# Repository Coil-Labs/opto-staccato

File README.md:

# opto-staccato

## Introduction
This is a pair of circuit boards (PCBs), known as the Opto-Staccato Controller and Receiver, which are a mains frequency synchronized interrupter for Tesla coils, primarily vacuum tube Tesla coils (VTTCs).

This circuit is based on the original Staccato Controller, created by Steve Ward https://www.stevehv.4hv.org/staccato.htm

This circuit is featured on the Coil Labs YouTube channel and is used to interrupt a large VTTC (https://youtu.be/IDOrxT_r8TY). This project was sponsored in part by PCBgogo (https://www.pcbgogo.com/), who provided the PCBs for this video.

The KiCad source files for both boards are available in this repository and the gerber files for both boards are available as .zip files in the Releases.

## Description

The Controller PCB detects the mains frequency zero crossing and then sends a pulse to the Receiver (with a controllable delay based on potentiometer RV1), signaling when to let the Tesla coil primary circuit to begin conducting. This signal is sent over a fiber optic link to protect the user from coming into contact with high voltage and enabling them to maintain a safe distance from the Tesla coil. The other controllable parameter (set by potentiometer RV2) of the Controller is the interrupter hold-off time, which enables the Tesla coil to be driven at integer factors of the mains frequency (e.g., 60 Hz, 30 Hz, 15 Hz, etc. in North America).

## Safety
WARNING! High voltage electricity and Tesla coils are dangerous and should not be handled or operated by anyone other than trained experts! 

## Usage
Jumpers J5 and J6 on the Controller and J7 and J8 on the Receiver enable using the PCBs in either 120V or 240V mains regions. Place two jumpers across pins 1 and 2 of both jumpers for 120V use or a single jumper across pin 2 of the two jumpers for 240V use, as indicated on the silk screen.

On the Controller, switch SW1 is the "phase-select" choosing to trigger the circuit on either the rising or falling mains zero crossing. Switch Sw2 is the "output-enable" switch, allowing the user to control when the Tesla coil interrupter is "turned on". Switch Sw3 selects the source of the signal being sent out via the fiber optic link; either the Staccato signal, "always on" for continuous wave operation, or an optional external 0-12V digital signal that can be provided via screw terminal J2.

The SCR or TRIAC used for Staccato operation is not included on the Receiver PCB as the choice of this component is specific to each Tesla coil. A screw terminal block J4 is provided to connect to the gate and cathode terminals for triggering. The selection of resistor R22 may need to be changed, depending on the gate voltage and current requirements of the SCR/TRIAC being used.

The fiber optic transmitter and receiver use standard 1000um core, 2.2mm jacket plastic fiber cable. The fuses are 500mA, 250V, fast blow, glass cartridge, 5mm x 20mm.

## License
These design files are published under the CERN Open Hardware License Version 2 - Weakly Reciprocal variant (CERN-OHL-W). Read more here (https://cern.ch/cern-ohl).

This is a copyleft, share-alike, open-source license. This means that you are free to redistribute, modify, or make derivatives these designs, and even commercialize them. But you MUST keep the redistributed, modified, or derivative designs open-source and under this or a compatible license. You CANNOT make modified or derivative designs proprietary; they MUST be kept open-source. This is different than a "permissive" open-source license, where you can make modifications or derivatives proprietary and then commercialize and profit off of your proprietary modification. You are absolutely free to commercialize and profit from modifications of this design, however, it must remain open-source and accessible to the public. Copyleft, share-alike is a philosophy. Scientific and engineering knowledge should not be kept as trade secrets and locked down under patents, owned by the wealthy, to only benefit the wealthy. Knowledge should be freely shared, always. Publishing scientific and engineering works under copyleft, share-alike licenses helps to create a more fair and democratic future where the hoarding of trade secrets is not a way to gain a competitive advantage. Please consider publishing your own works under such a license.

## Controller Schematic

## Receiver Schematic

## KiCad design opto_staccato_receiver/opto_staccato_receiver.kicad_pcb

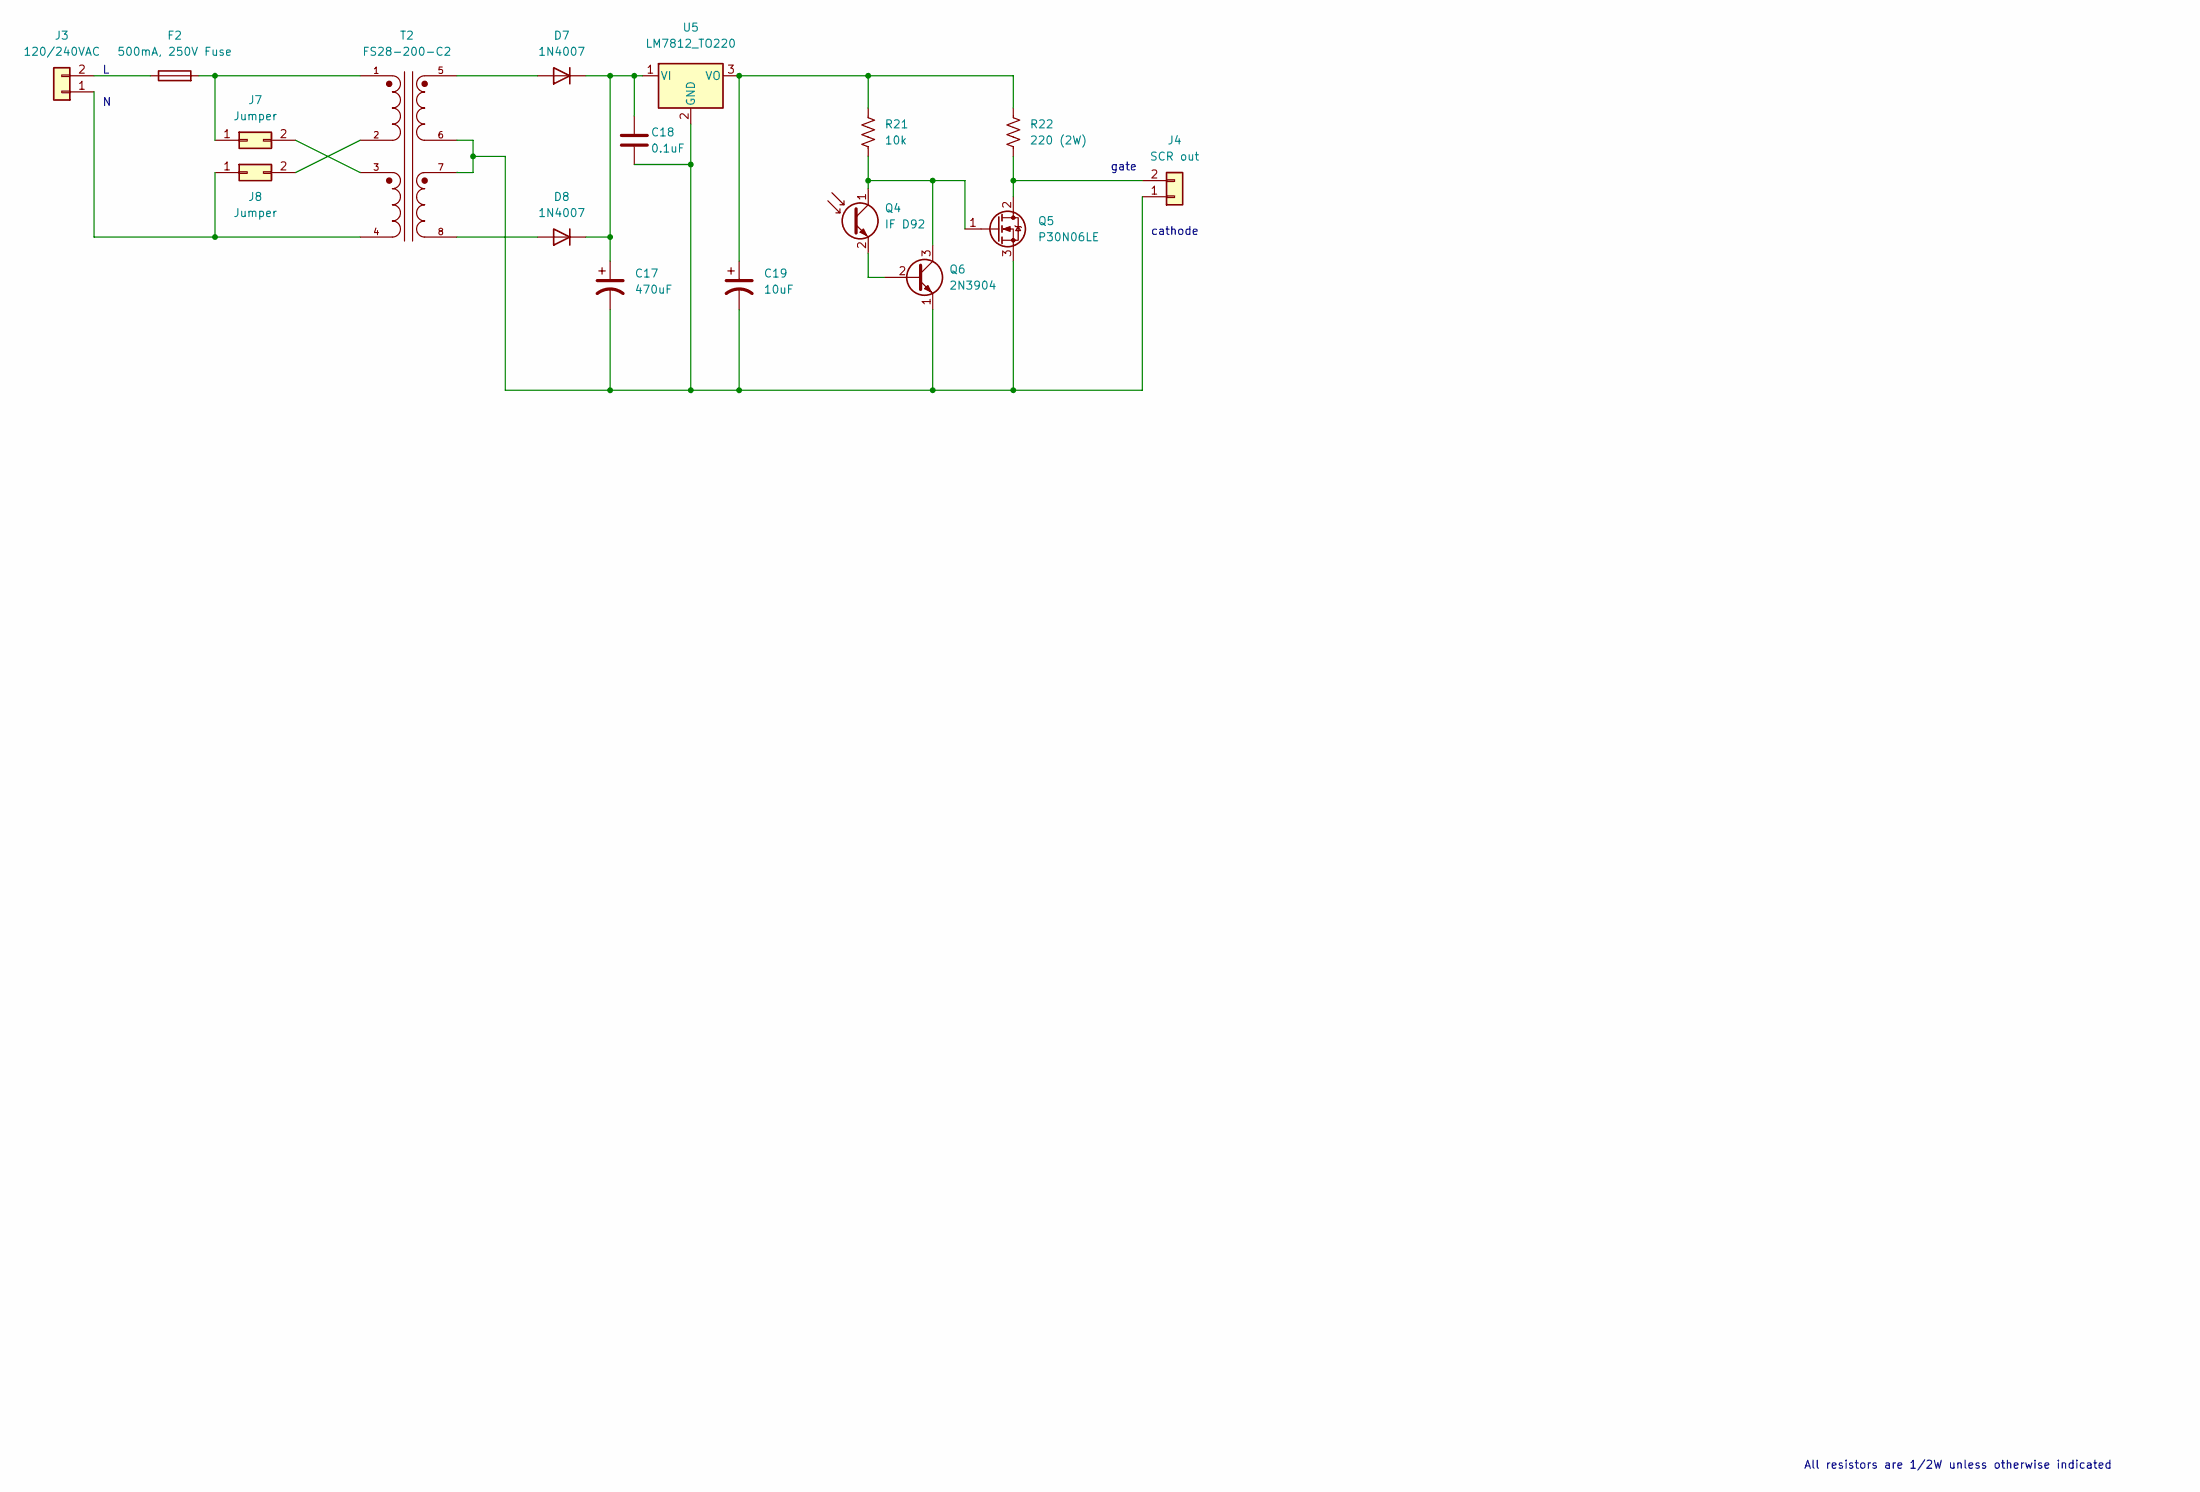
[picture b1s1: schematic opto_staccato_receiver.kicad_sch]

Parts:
C17: 470uF; CP_Radial_D10.0mm_P5.00mm
C18: 0.1uF; C_Disc_D4.7mm_W2.5mm_P5.00mm
C19: 10uF; CP_Radial_D5.0mm_P2.00mm
D7, D8: 1N4007; D_DO-41_SOD81_P10.16mm_Horizontal
F2: 500mA, 250V Fuse; 0PTF0078P
J3: 120/240VAC; SolderWire-1sqmm_1x02_P5.4mm_D1.4mm_OD2.7mm
J4: SCR out; CUI_TB007-508-02GR
J7, J8: Jumper; PinHeader_2x01_P2.54mm_Vertical
Q4: IF D92; IF-E91A
Q5: P30N06LE; TO-220-3_Vertical
Q6: 2N3904; TO-92_Inline
R21: 10k; R_Axial_DIN0309_L9.0mm_D3.2mm_P12.70mm_Horizontal
R22: 220 (2W); R_Axial_DIN0516_L15.5mm_D5.0mm_P20.32mm_Horizontal
T2: FS28-200-C2; TRANSFORMER_FS28-200-C2
U5: LM7812_TO220; TO-220-3_Vertical

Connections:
unnamed: C17.1, C18.1, D7.1 (K), D8.1 (K), U5.1 (VI)
unnamed: C17.2, C18.2, C19.2, J4.1, Q5.3 (S), Q6.1 (E), T2.6, T2.7, U5.2 (GND)
unnamed: C19.1, R21.1, R22.1, U5.3 (VO)
unnamed: D7.2 (A), T2.5
unnamed: D8.2 (A), T2.8
unnamed: F2.1, J3.2
unnamed: F2.2, J7.1, T2.1
unnamed: J3.1, J8.1, T2.4
unnamed: J4.2, Q5.2 (D), R22.2
unnamed: J7.2, T2.3
unnamed: J8.2, T2.2
unnamed: Q4.1 (C), Q5.1 (G), Q6.3 (C), R21.2
unnamed: Q4.2 (E), Q6.2 (B)

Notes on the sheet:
gate
cathode
All resistors are 1/2W unless otherwise indicated

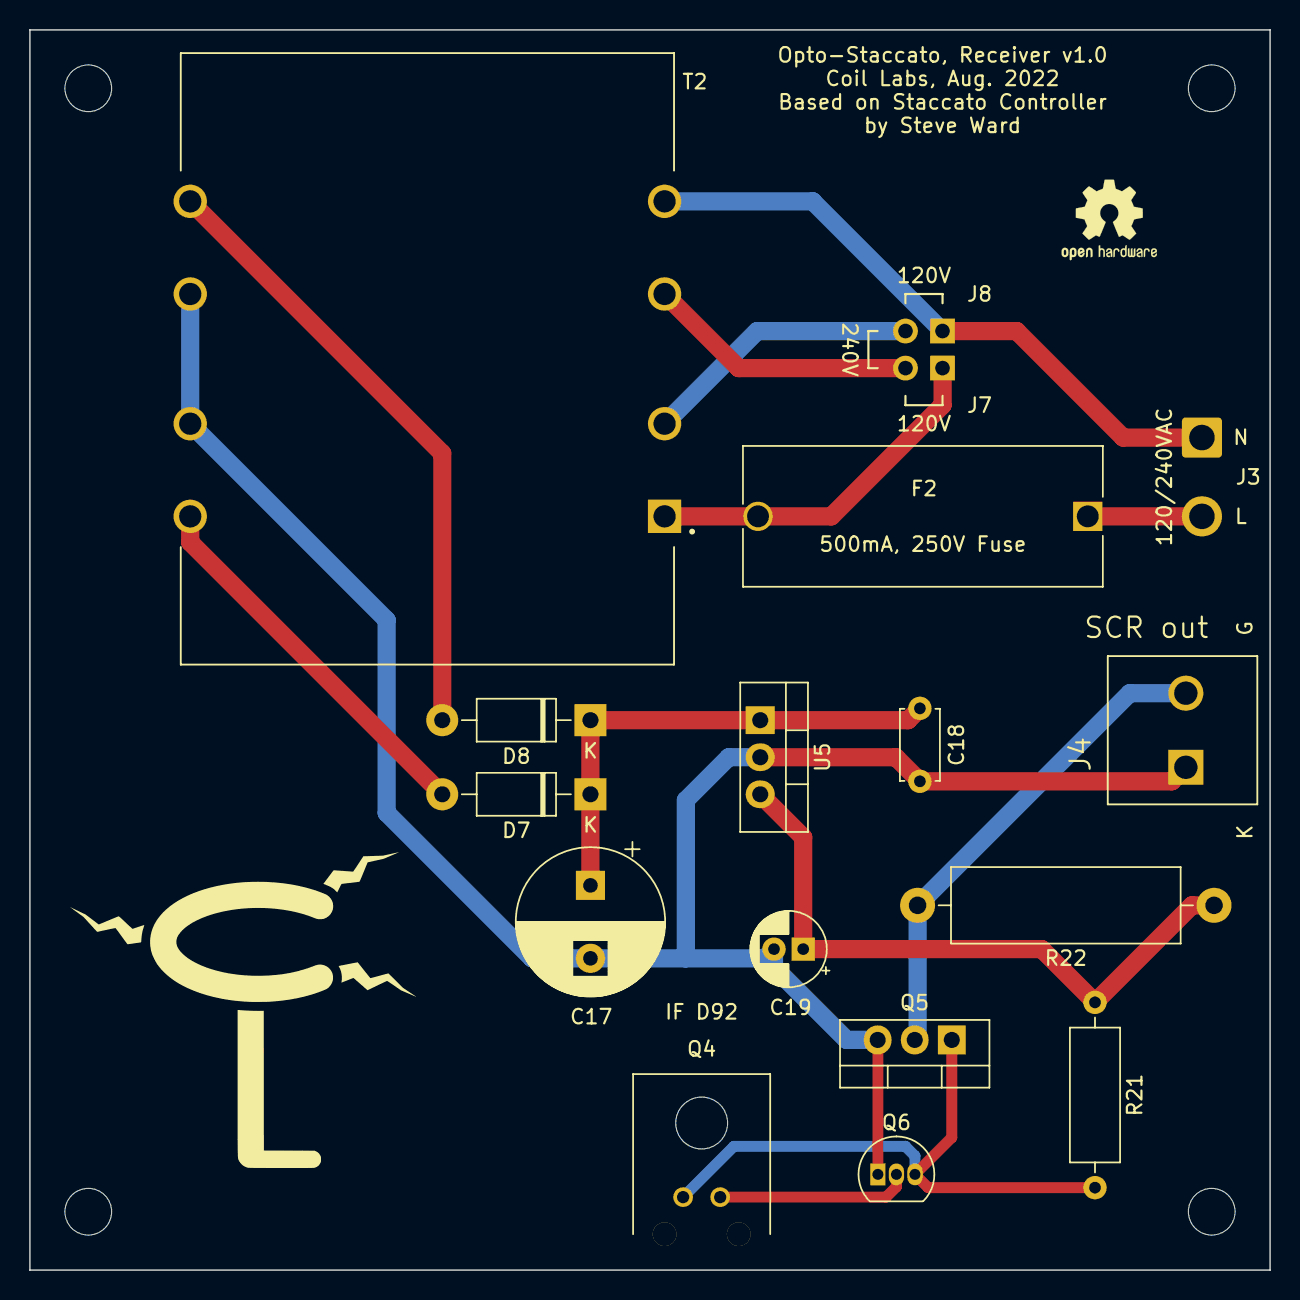
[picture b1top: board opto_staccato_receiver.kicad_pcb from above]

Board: 2 copper layers, 85.0 x 85.0 mm, 17 parts (0 on the bottom side), 13 nets.

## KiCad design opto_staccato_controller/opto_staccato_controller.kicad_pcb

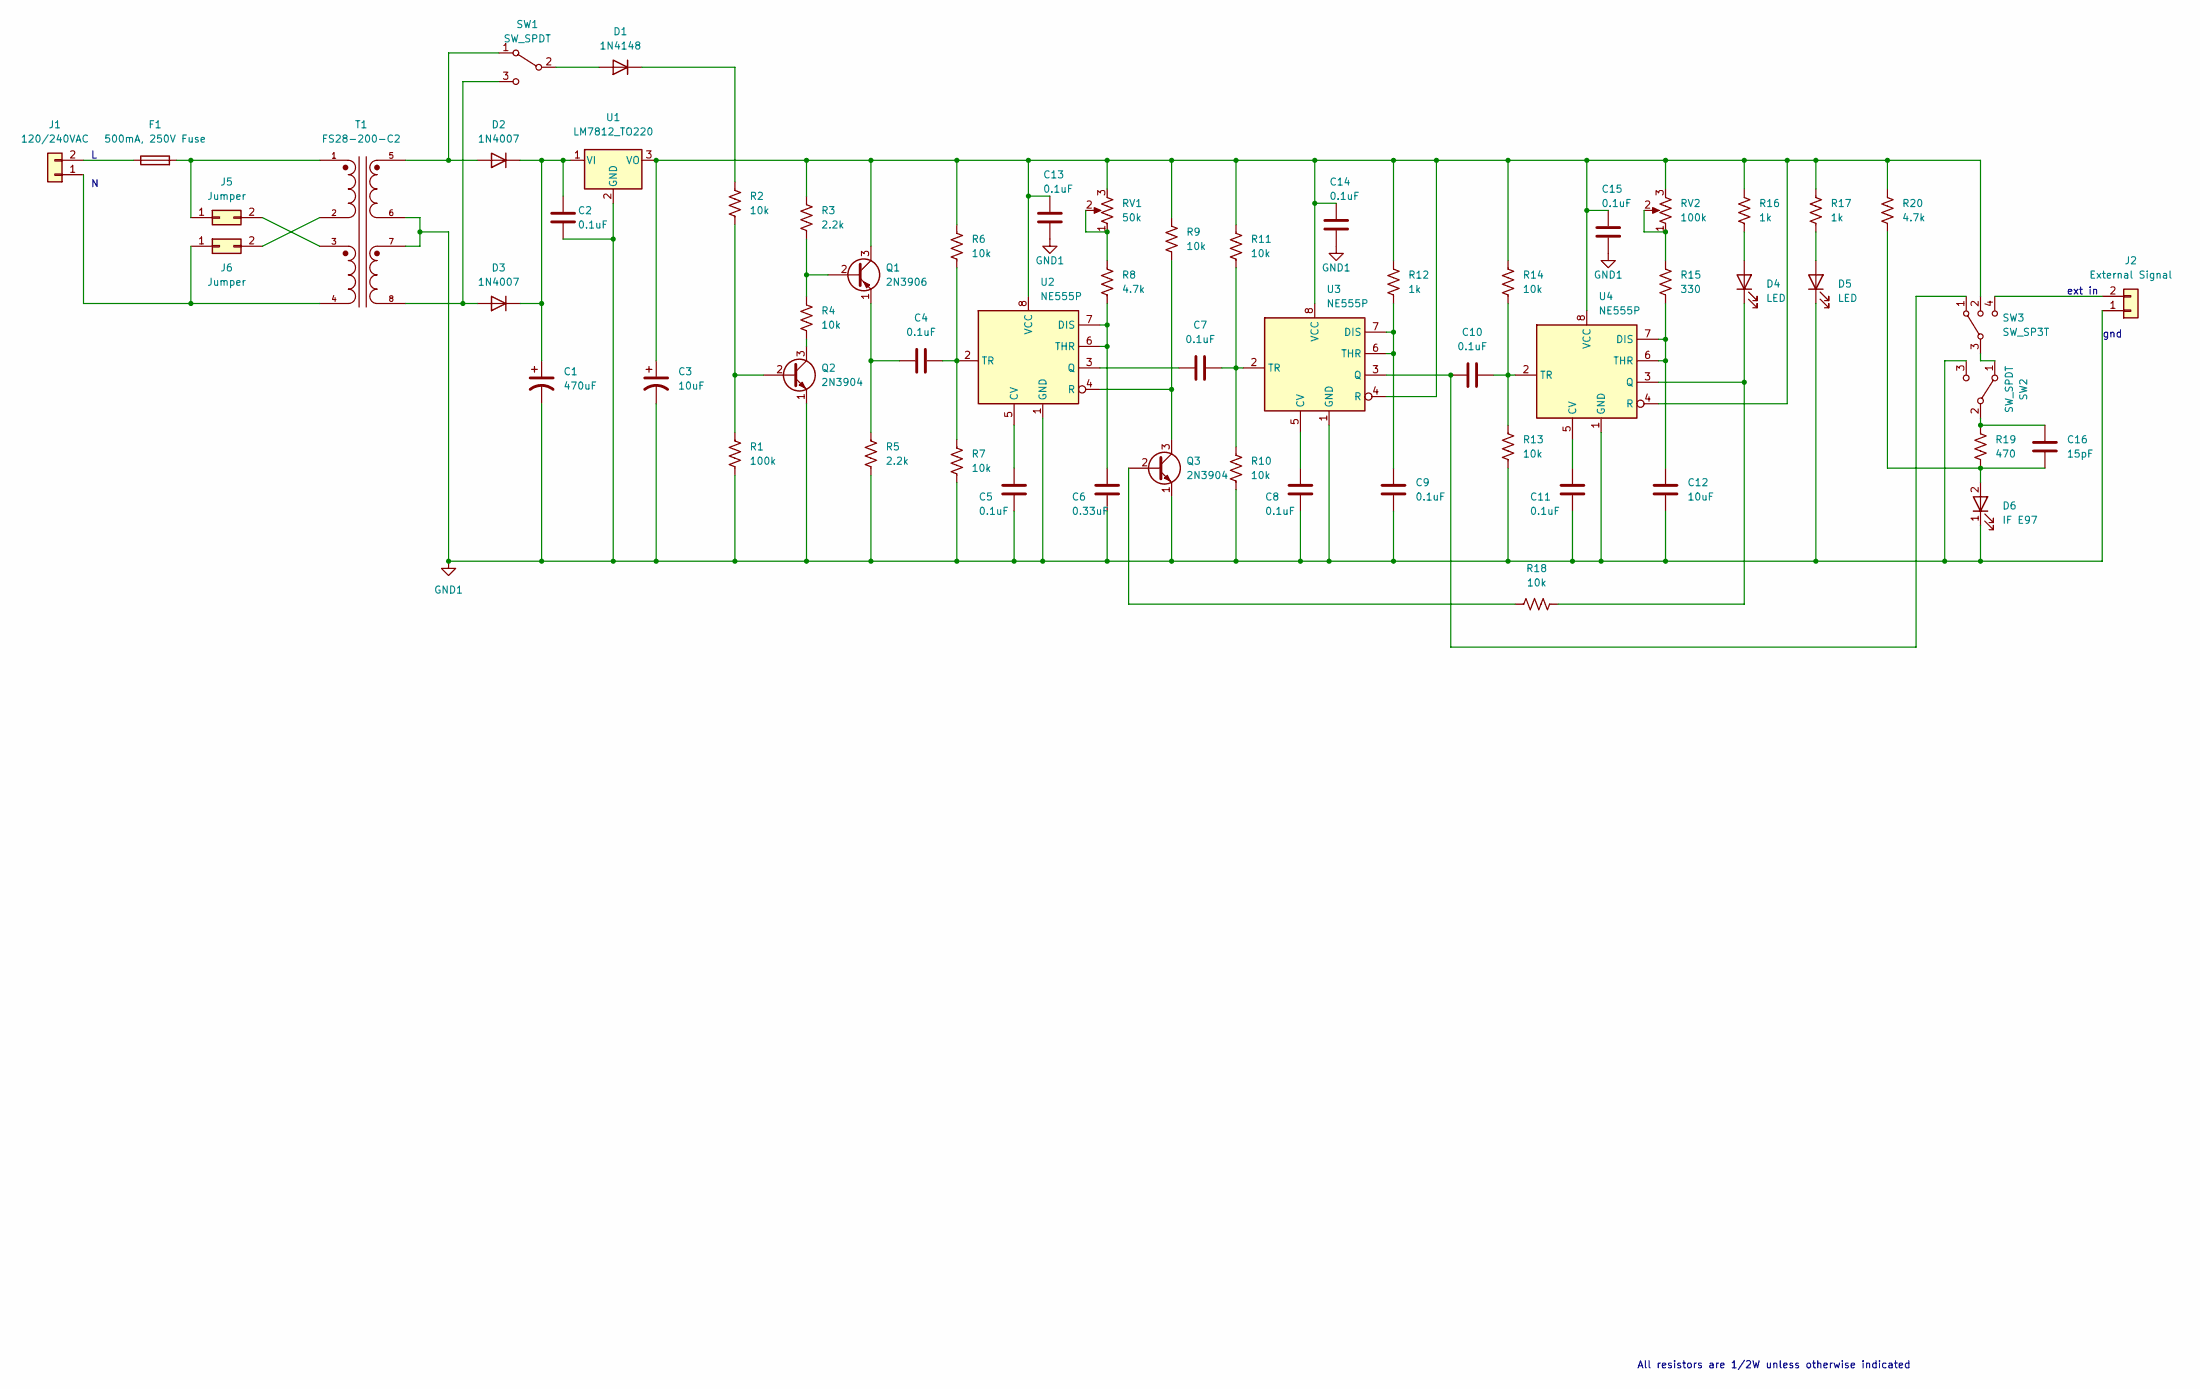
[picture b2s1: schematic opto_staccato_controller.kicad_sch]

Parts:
C1: 470uF; CP_Radial_D10.0mm_P5.00mm
C2, C4, C5, C7, C8, C9, C10, C11, C13, C14, C15: 0.1uF; C_Disc_D4.7mm_W2.5mm_P5.00mm
C3: 10uF; CP_Radial_D5.0mm_P2.00mm
C6: 0.33uF; C_Disc_D6.0mm_W4.4mm_P5.00mm
C12: 10uF; C_Disc_D5.1mm_W3.2mm_P5.00mm
C16: 15pF; C_Disc_D4.7mm_W2.5mm_P5.00mm
D1: 1N4148; D_DO-35_SOD27_P7.62mm_Horizontal
D2, D3: 1N4007; D_DO-41_SOD81_P10.16mm_Horizontal
D4, D5: LED; LED_D5.0mm_Clear
D6: IF E97; IF-E91A
F1: 500mA, 250V Fuse; 0PTF0078P
J1: 120/240VAC; SolderWire-1sqmm_1x02_P5.4mm_D1.4mm_OD2.7mm
J2: External Signal; CUI_TB007-508-02GR
J5, J6: Jumper; PinHeader_2x01_P2.54mm_Vertical
Q1: 2N3906; TO-92_Inline
Q2, Q3: 2N3904; TO-92_Inline
R1: 100k; R_Axial_DIN0309_L9.0mm_D3.2mm_P12.70mm_Horizontal
R2, R4, R6, R7, R9, R10, R11, R13, R14, R18: 10k; R_Axial_DIN0309_L9.0mm_D3.2mm_P12.70mm_Horizontal
R3, R5: 2.2k; R_Axial_DIN0309_L9.0mm_D3.2mm_P12.70mm_Horizontal
R8, R20: 4.7k; R_Axial_DIN0309_L9.0mm_D3.2mm_P12.70mm_Horizontal
R12, R16, R17: 1k; R_Axial_DIN0309_L9.0mm_D3.2mm_P12.70mm_Horizontal
R15: 330; R_Axial_DIN0309_L9.0mm_D3.2mm_P12.70mm_Horizontal
R19: 470; R_Axial_DIN0309_L9.0mm_D3.2mm_P12.70mm_Horizontal
RV1: 50k; SolderWire-0.5sqmm_1x03_P4.6mm_D0.9mm_OD2.1mm
RV2: 100k; SolderWire-0.5sqmm_1x03_P4.6mm_D0.9mm_OD2.1mm
SW1, SW2: SW_SPDT; SolderWire-0.5sqmm_1x03_P4.6mm_D0.9mm_OD2.1mm
SW3: SW_SP3T; SolderWire-0.5sqmm_1x04_P4.6mm_D0.9mm_OD2.1mm
T1: FS28-200-C2; TRANSFORMER_FS28-200-C2
U1: LM7812_TO220; TO-220-3_Vertical
U2, U3, U4: NE555P; DIP-8_W7.62mm

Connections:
GND1: C1.2, C2.2, C3.2, C5.2, C6.2, C8.2, C9.2, C11.2, C12.2, C13.2, C14.2, C15.2, D5.1 (K), D6.1 (K), J2.1, Q2.1 (E), Q3.1 (E), R1.2, R5.2, R7.2, R10.2, R13.2, SW2.3 (C), T1.6, T1.7, U1.2 (GND), U2.1 (GND), U3.1 (GND), U4.1 (GND)
unnamed: C1.1, C2.1, D2.1 (K), D3.1 (K), U1.1 (VI)
unnamed: C4.1, Q1.1 (E), R5.1
unnamed: C4.2, R6.2, R7.1, U2.2 (TR)
unnamed: C5.1, U2.5 (CV)
unnamed: C6.1, R8.2, U2.6 (THR), U2.7 (DIS)
unnamed: C7.1, R10.1, R11.2, U3.2 (TR)
unnamed: C7.2, U2.3 (Q)
unnamed: C8.1, U3.5 (CV)
unnamed: C9.1, R12.2, U3.6 (THR), U3.7 (DIS)
unnamed: C10.1, SW3.1, U3.3 (Q)
unnamed: C10.2, R13.1, R14.2, U4.2 (TR)
unnamed: C11.1, U4.5 (CV)
unnamed: C12.1, R15.2, U4.6 (THR), U4.7 (DIS)
unnamed: C3.1, C13.1, C14.1, C15.1, Q1.3 (C), R3.1, R6.1, R9.1, R11.1, R12.1, R14.1, R16.1, R17.1, R20.1, RV1.3, RV2.3, SW3.2, U1.3 (VO), U2.8 (VCC), U3.4 (R), U3.8 (VCC), U4.4 (R), U4.8 (VCC)
unnamed: C16.1, R19.1, SW2.2 (B)
unnamed: C16.2, D6.2 (A), R19.2, R20.2
unnamed: D1.1 (K), R2.1
unnamed: D1.2 (A), SW1.2 (B)
unnamed: D2.2 (A), SW1.1 (A), T1.5
unnamed: D3.2 (A), SW1.3 (C), T1.8
unnamed: D4.1 (K), R18.2, U4.3 (Q)
unnamed: D4.2 (A), R16.2
unnamed: D5.2 (A), R17.2
unnamed: F1.1, J1.2
unnamed: F1.2, J5.1, T1.1
unnamed: J1.1, J6.1, T1.4
unnamed: J2.2, SW3.4
unnamed: J5.2, T1.3
unnamed: J6.2, T1.2
unnamed: Q1.2 (B), R3.2, R4.1
unnamed: Q2.2 (B), R1.1, R2.2
unnamed: Q2.3 (C), R4.2
unnamed: Q3.2 (B), R18.1
unnamed: Q3.3 (C), R9.2, U2.4 (R)
unnamed: R8.1, RV1.1, RV1.2
unnamed: R15.1, RV2.1, RV2.2
unnamed: SW2.1 (A), SW3.3

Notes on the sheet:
All resistors are 1/2W unless otherwise indicated
ext in
gnd

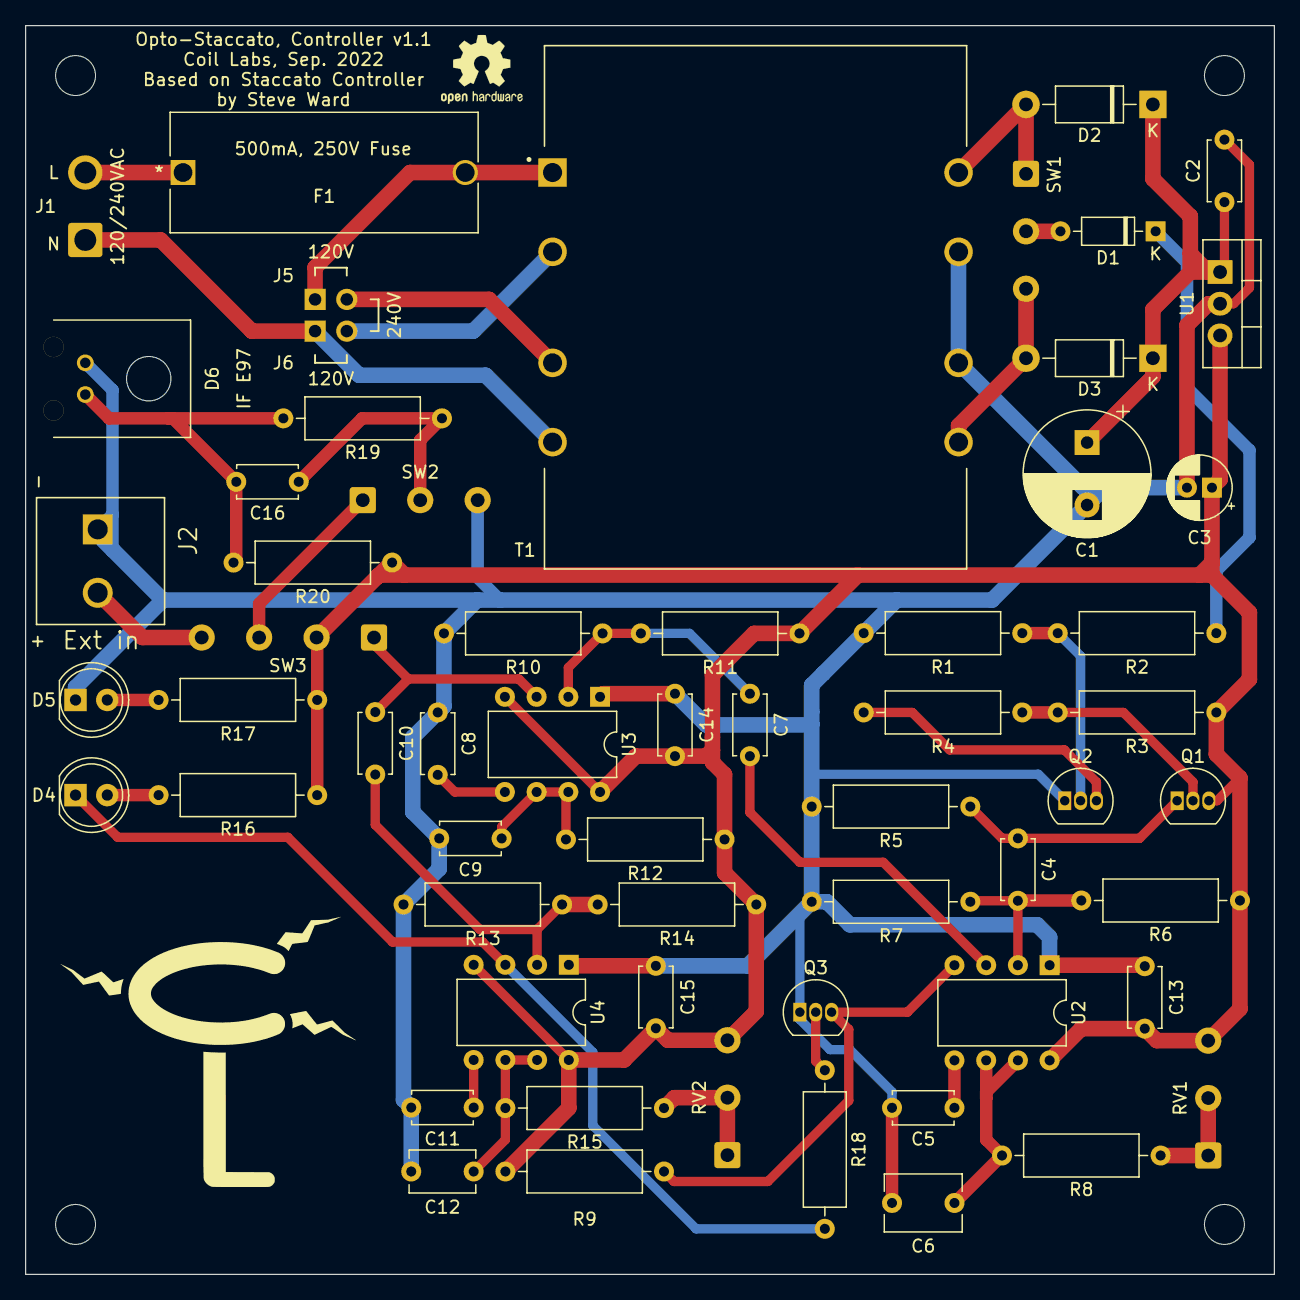
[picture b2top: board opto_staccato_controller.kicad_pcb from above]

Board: 2 copper layers, 100.0 x 100.0 mm, 60 parts (0 on the bottom side), 38 nets.

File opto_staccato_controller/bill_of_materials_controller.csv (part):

Date:,Mon 26 Sep 2022 07:49:17 PM EDT,,,,,,,,,,,
Tool:,Eeschema 6.0.7-f9a2dced07~116~ubuntu20.04.1,,,,,,,,,,,
Component Count:,60,,,,,,,,,,,
,,,,,,,,,,,,
Individual Components:,,,,,,,,,,,,
,,,,,,,,,,,,
Item,Qty,Reference(s),Value,LibPart,Footprint,Datasheet,MANUFACTURER,STANDARD,Spice_Lib_File,Spice_Model,Spice_Netlist_Enabled,Spice_Primitive
,,C1,470uF,Device:C_Polarized_US,Capacitor_THT:CP_Radial_D10.0mm_P5.00mm,~,,,,470u,Y,C
,,C2,0.1uF,Device:C,Capacitor_THT:C_Disc_D4.7mm_W2.5mm_P5.00mm,~,,,,0.1u,Y,C
,,C3,10uF,Device:C_Polarized_US,Capacitor_THT:CP_Radial_D5.0mm_P2.00mm,~,,,,10u,Y,C
,,C4,0.1uF,Device:C,Capacitor_THT:C_Disc_D4.7mm_W2.5mm_P5.00mm,~,,,,0.1u,Y,C
,,C5,0.1uF,Device:C,Capacitor_THT:C_Disc_D4.7mm_W2.5mm_P5.00mm,~,,,,,,
,,C6,0.33uF,Device:C,Capacitor_THT:C_Disc_D6.0mm_W4.4mm_P5.00mm,~,,,,,,
,,C7,0.1uF,Device:C,Capacitor_THT:C_Disc_D4.7mm_W2.5mm_P5.00mm,~,,,,,,
,,C8,0.1uF,Device:C,Capacitor_THT:C_Disc_D4.7mm_W2.5mm_P5.00mm,~,,,,0.1u,Y,C
,,C9,0.1uF,Device:C,Capacitor_THT:C_Disc_D4.7mm_W2.5mm_P5.00mm,~,,,,0.2u,Y,C
,,C10,0.1uF,Device:C,Capacitor_THT:C_Disc_D4.7mm_W2.5mm_P5.00mm,~,,,,0.001u,Y,C
,,C11,0.1uF,Device:C,Capacitor_THT:C_Disc_D4.7mm_W2.5mm_P5.00mm,~,,,,0.1u,Y,C
,,C12,10uF,Device:C,Capacitor_THT:C_Disc_D5.1mm_W3.2mm_P5.00mm,~,,,,10u,Y,C
,,C13,0.1uF,Device:C,Capacitor_THT:C_Disc_D4.7mm_W2.5mm_P5.00mm,~,,,,,,
,,C14,0.1uF,Device:C,Capacitor_THT:C_Disc_D4.7mm_W2.5mm_P5.00mm,~,,,,,,
,,C15,0.1uF,Device:C,Capacitor_THT:C_Disc_D4.7mm_W2.5mm_P5.00mm,~,,,,,,
,,C16,15pF,Device:C,Capacitor_THT:C_Disc_D4.7mm_W2.5mm_P5.00mm,~,,,,,,
,,D1,1N4148,Diode:1N4007,Diode_THT:D_DO-35_SOD27_P7.62mm_Horizontal,http://www.vishay.com/docs/88503/1n4001.pdf,,,,1N4007,Y,D
,,D2,1N4007,Diode:1N4007,Diode_THT:D_DO-41_SOD81_P10.16mm_Horizontal,http://www.vishay.com/docs/88503/1n4001.pdf,,,,1N4007,Y,D
,,D3,1N4007,Diode:1N4007,Diode_THT:D_DO-41_SOD81_P10.16mm_Horizontal,http://www.vishay.com/docs/88503/1n4001.pdf,,,,1N4007,Y,D
,,D4,LED,Device:LED,LED_THT:LED_D5.0mm_Clear,~,,,,LED_GENERAL,Y,D
,,D5,LED,Device:LED,LED_THT:LED_D5.0mm_Clear,~,,,,LED_GENERAL,Y,D
,,D6,IF E97,:LED_1,IF-E91A:IF-E91A,~,,,,,,
,,F1,"500mA, 250V Fuse",Device:Fuse,0PTF0078P:0PTF0078P,~,,,,,,
,,J1,120/240VAC,Connector_Generic:Conn_01x02,Connector_Wire:SolderWire-1sqmm_1x02_P5.4mm_D1.4mm_OD2.7mm,~,,,,,,
,,J2,External Signal,Connector_Generic:Conn_01x02,TB007-508-02GR:CUI_TB007-508-02GR,~,,,,,,
,,J5,Jumper,Connector_Generic:Conn_02x01,Connector_PinHeader_2.54mm:PinHeader_2x01_P2.54mm_Vertical,~,,,,,,
,,J6,Jumper,Connector_Generic:Conn_02x01,Connector_PinHeader_2.54mm:PinHeader_2x01_P2.54mm_Vertical,~,,,,,,
,,Q1,2N3906,Transistor_BJT:2N3906,Package_TO_SOT_THT:TO-92_Inline,https://www.onsemi.com/pub/Collateral/2N3906-D.PDF,,,,2N3906,Y,Q
,,Q2,2N3904,Transistor_BJT:2N3904,Package_TO_SOT_THT:TO-92_Inline,https://www.onsemi.com/pub/Collateral/2N3903-D.PDF,,,,2N3904,Y,Q
,,Q3,2N3904,Transistor_BJT:2N3904,Package_TO_SOT_THT:TO-92_Inline,https://www.onsemi.com/pub/Collateral/2N3903-D.PDF,,,,2N3904,Y,Q
,,R1,100k,Device:R_US,Resistor_THT:R_Axial_DIN0309_L9.0mm_D3.2mm_P12.70mm_Horizontal,~,,,,100k,Y,R
,,R2,10k,Device:R_US,Resistor_THT:R_Axial_DIN0309_L9.0mm_D3.2mm_P12.70mm_Horizontal,~,,,,10k,Y,R
,,R3,2.2k,Device:R_US,Resistor_THT:R_Axial_DIN0309_L9.0mm_D3.2mm_P12.70mm_Horizontal,~,,,,2.2k,Y,R
,,R4,10k,Device:R_US,Resistor_THT:R_Axial_DIN0309_L9.0mm_D3.2mm_P12.70mm_Horizontal,~,,,,10k,Y,R
,,R5,2.2k,Device:R_US,Resistor_THT:R_Axial_DIN0309_L9.0mm_D3.2mm_P12.70mm_Horizontal,~,,,,2.2k,Y,R
,,R6,10k,Device:R_US,Resistor_THT:R_Axial_DIN0309_L9.0mm_D3.2mm_P12.70mm_Horizontal,~,,,,100k,Y,R
,,R7,10k,Device:R_US,Resistor_THT:R_Axial_DIN0309_L9.0mm_D3.2mm_P12.70mm_Horizontal,~,,,,100k,Y,R
,,R8,4.7k,Device:R_US,Resistor_THT:R_Axial_DIN0309_L9.0mm_D3.2mm_P12.70mm_Horizontal,~,,,,,,
,,R9,10k,Device:R_US,Resistor_THT:R_Axial_DIN0309_L9.0mm_D3.2mm_P12.70mm_Horizontal,~,,,,10k,Y,R
,,R10,10k,Device:R_US,Resistor_THT:R_Axial_DIN0309_L9.0mm_D3.2mm_P12.70mm_Horizontal,~,,,,,,
,,R11,10k,Device:R_US,Resistor_THT:R_Axial_DIN0309_L9.0mm_D3.2mm_P12.70mm_Horizontal,~,,,,,,
,,R12,1k,Device:R_US,Resistor_THT:R_Axial_DIN0309_L9.0mm_D3.2mm_P12.70mm_Horizontal,~,,,,1k,Y,R
,,R13,10k,Device:R_US,Resistor_THT:R_Axial_DIN0309_L9.0mm_D3.2mm_P12.70mm_Horizontal,~,,,,10k,Y,R
,,R14,10k,Device:R_US,Resistor_THT:R_Axial_DIN0309_L9.0mm_D3.2mm_P12.70mm_Horizontal,~,,,,10k,Y,R
,,R15,330,Device:R_US,Resistor_THT:R_Axial_DIN0309_L9.0mm_D3.2mm_P12.70mm_Horizontal,~,,,,1k,Y,R
,,R16,1k,Device:R_US,Resistor_THT:R_Axial_DIN0309_L9.0mm_D3.2mm_P12.70mm_Horizontal,~,,,,1k,Y,R
,,R17,1k,Device:R_US,Resistor_THT:R_Axial_DIN0309_L9.0mm_D3.2mm_P12.70mm_Horizontal,~,,,,1k,Y,R
,,R18,10k,Device:R_US,Resistor_THT:R_Axial_DIN0309_L9.0mm_D3.2mm_P12.70mm_Horizontal,~,,,,10k,Y,R
,,R19,470,Device:R_US,Resistor_THT:R_Axial_DIN0309_L9.0mm_D3.2mm_P12.70mm_Horizontal,~,,,,,,
,,R20,4.7k,Device:R_US,Resistor_THT:R_Axial_DIN0309_L9.0mm_D3.2mm_P12.70mm_Horizontal,~,,,,1k,Y,R
,,RV1,50k,Device:R_Potentiometer_US,Connector_Wire:SolderWire-0.5sqmm_1x03_P4.6mm_D0.9mm_OD2.1mm,~,,,,,,
,,RV2,100k,Device:R_Potentiometer_US,Connector_Wire:SolderWire-0.5sqmm_1x03_P4.6mm_D0.9mm_OD2.1mm,~,,,,pot50k,Y,X
,,SW1,SW_SPDT,Switch:SW_SPDT,Connector_Wire:SolderWire-0.5sqmm_1x03_P4.6mm_D0.9mm_OD2.1mm,~,,,,,,
,,SW2,SW_SPDT,Switch:SW_SPDT,Connector_Wire:SolderWire-0.5sqmm_1x03_P4.6mm_D0.9mm_OD2.1mm,~,,,,,,
,,SW3,SW_SP3T,Switch:SW_SP3T,Connector_Wire:SolderWire-0.5sqmm_1x04_P4.6mm_D0.9mm_OD2.1mm,~,,,,,,
,,T1,FS28-200-C2,FS28-200-C2:FS28-200-C2,FS28-200-C2:TRANSFORMER_FS28-200-C2,,Triad,Manufacturer Recommendations,,,,
,,U1,LM7812_TO220,Regulator_Linear:LM7812_TO220,Package_TO_SOT_THT:TO-220-3_Vertical,https://www.onsemi.cn/PowerSolutions/document/MC7800-D.PDF,,,,LM7812,Y,X
,,U2,NE555P,Timer:NE555P,Package_DIP:DIP-8_W7.62mm,http://www.ti.com/lit/ds/symlink/ne555.pdf,,,,NE555,Y,X
,,U3,NE555P,Timer:NE555P,Package_DIP:DIP-8_W7.62mm,http://www.ti.com/lit/ds/symlink/ne555.pdf,,,,NE555,Y,X
,,U4,NE555P,Timer:NE555P,Package_DIP:DIP-8_W7.62mm,http://www.ti.com/lit/ds/symlink/ne555.pdf,,,,NE555,Y,X
,,,,,,,,,,,,
,,,,,,,,,,,,
,,,,,,,,,,,,
Collated Components:,,,,,,,,,,,,
,,,,,,,,,,,,
Item,Qty,Reference(s),Value,LibPart,Footprint,Datasheet,MANUFACTURER,STANDARD,Spice_Lib_File,Spice_Model,Spice_Netlist_Enabled,Spice_Primitive
1,1,C1,470uF,Device:C_Polarized_US,Capacitor_THT:CP_Radial_D10.0mm_P5.00mm,~,,,,470u,Y,C
2,11,"C2, C4, C5, C7, C8, C9, C10, C11, C13, C14, C15",0.1uF,Device:C,Capacitor_THT:C_Disc_D4.7mm_W2.5mm_P5.00mm,~,,,,0.1u,Y,C
3,1,C3,10uF,Device:C_Polarized_US,Capacitor_THT:CP_Radial_D5.0mm_P2.00mm,~,,,,10u,Y,C
4,1,C6,0.33uF,Device:C,Capacitor_THT:C_Disc_D6.0mm_W4.4mm_P5.00mm,~,,,,,,
5,1,C12,10uF,Device:C,Capacitor_THT:C_Disc_D5.1mm_W3.2mm_P5.00mm,~,,,,10u,Y,C
6,1,C16,15pF,Device:C,Capacitor_THT:C_Disc_D4.7mm_W2.5mm_P5.00mm,~,,,,,,
7,1,D1,1N4148,Diode:1N4007,Diode_THT:D_DO-35_SOD27_P7.62mm_Horizontal,http://www.vishay.com/docs/88503/1n4001.pdf,,,/media/nick/3TB_HDD/College Documents/Personal/Coil Labs Files/kicad_spice_library/Models/Diode/DIODE2.lib,1N4007,Y,D
8,2,"D2, D3",1N4007,Diode:1N4007,Diode_THT:D_DO-41_SOD81_P10.16mm_Horizontal,http://www.vishay.com/docs/88503/1n4001.pdf,,,/media/nick/3TB_HDD/College Documents/Personal/Coil Labs Files/kicad_spice_library/Models/Diode/DIODE2.lib,1N4007,Y,D
9,2,"D4, D5",LED,Device:LED,LED_THT:LED_D5.0mm_Clear,~,,,/media/nick/3TB_HDD/College Documents/Personal/Coil Labs Files/kicad_spice_library/Models/Diode/led.lib,LED_GENERAL,Y,D
10,1,D6,IF E97,:LED_1,IF-E91A:IF-E91A,~,,,,,,
11,1,F1,"500mA, 250V Fuse",Device:Fuse,0PTF0078P:0PTF0078P,~,,,,,,
12,1,J1,120/240VAC,Connector_Generic:Conn_01x02,Connector_Wire:SolderWire-1sqmm_1x02_P5.4mm_D1.4mm_OD2.7mm,~,,,,,,
13,1,J2,External Signal,Connector_Generic:Conn_01x02,TB007-508-02GR:CUI_TB007-508-02GR,~,,,,,,
14,2,"J5, J6",Jumper,Connector_Generic:Conn_02x01,Connector_PinHeader_2.54mm:PinHeader_2x01_P2.54mm_Vertical,~,,,,,,
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
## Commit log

2022-09-27 Update README with details
2022-09-27 Add license to source files and images of schematics
2022-09-27 Add images of schematics to README
2022-09-28 Mention gerber files in releases in README

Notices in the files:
parts and their libraries:
Copyright 2021 Accelerated Designs. All rights reserved.
